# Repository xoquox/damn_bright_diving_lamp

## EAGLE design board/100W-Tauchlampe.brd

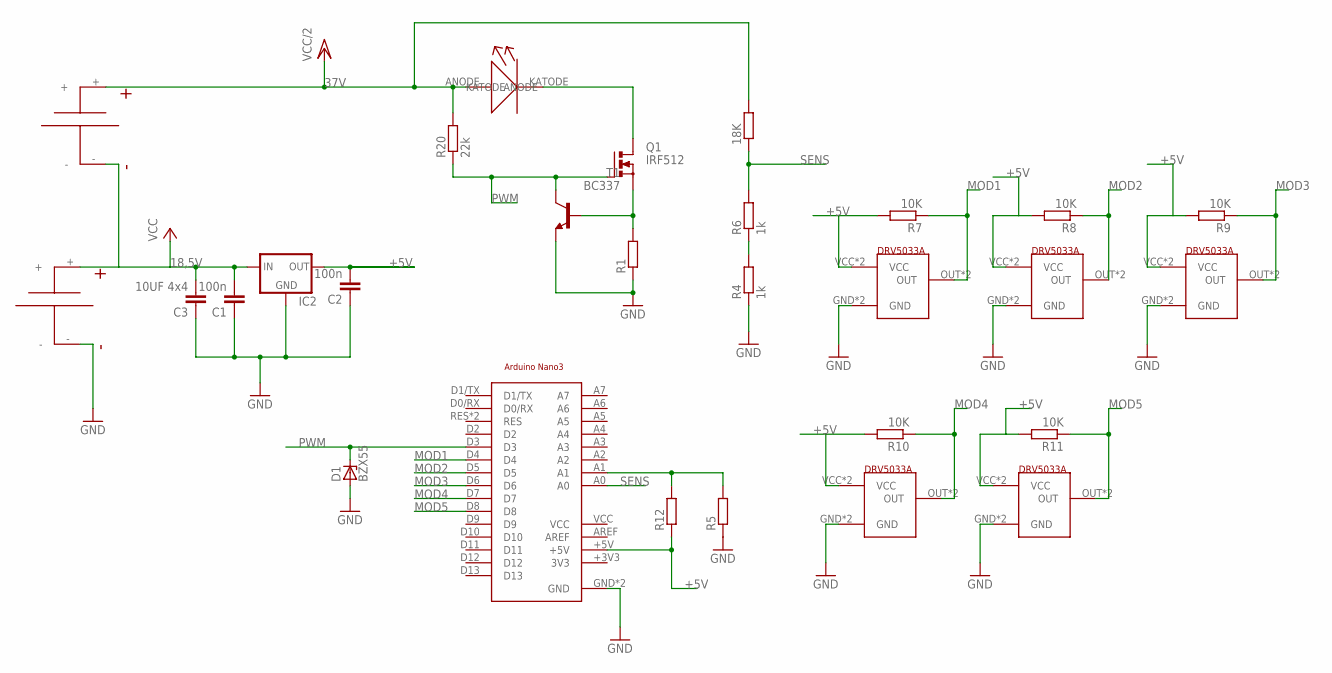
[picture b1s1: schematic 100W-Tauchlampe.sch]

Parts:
1, 2, 3, 4, 5: DRV5033AJQLPGM; T92/SOT23
18K: R-EU_R0805; R0805
C1, C2: 100n; C0603
C3: 10UF 4x4; 4X4
D1: BZX55; DO35Z10
IC2: 78XXS
Q1: IRF512; TO220BV
R1: R-EU_0207/2V; 0207/2V
R4, R6: 1k; R0805
R5: R-EU_R0805; R0805
R7, R8, R9, R10, R11: 10K; R0805
R12: R-EU_0204/2V; 0204V
R20: 22k; 0204V
T1: BC337; TO92
U$1: ARDUINO-NANO3
U$7: 100W-LED
U$8, U$9: AKKU; AKKUSMD

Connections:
18,5V: C1.2, C3.P$2 (2), IC2.IN, U$8.-, U$9.+
37V: 18K.2, R20.2, U$7.ANODE, U$8.+
+5V: 2.VCC, 2.VCC/SMD (VCC), 3.VCC, 3.VCC/SMD (VCC), 5.VCC, 5.VCC/SMD (VCC), C2.2, IC2.OUT, R8.2, R9.2, R11.2, R12.1, U$1.+5V
GND: 1.GND, 1.GND/SMD (GND), 2.GND, 2.GND/SMD (GND), 3.GND, 3.GND/SMD (GND), 4.GND, 4.GND/SMD (GND), 5.GND, 5.GND/SMD (GND), C1.1, C2.1, C3.1, D1.A, IC2.GND, R1.1, R4.1, R5.1, T1.1 (E), U$1.GND, U$1.GND2 (GND), U$9.-
MOD1: 1.OUT, 1.OUT/SMD (OUT), R7.1, U$1.D4
MOD2: 2.OUT, 2.OUT/SMD (OUT), R8.1, U$1.D5
MOD3: 3.OUT, 3.OUT/SMD (OUT), R9.1, U$1.D6
MOD4: 4.OUT, 4.OUT/SMD (OUT), R10.1, U$1.D7
MOD5: 5.OUT, 5.OUT/SMD (OUT), R11.1, U$1.D8
unnamed: R5.2, R12.2, U$1.A1
unnamed: Q1.S, R1.2, T1.2 (B)
unnamed: 1.VCC, 1.VCC/SMD (VCC), R7.2
unnamed: Q1.D, U$7.KATODE
unnamed: 4.VCC, 4.VCC/SMD (VCC), R10.2
unnamed: R4.2, R6.1
PWM: D1.C, Q1.G, R20.1, T1.3 (C), U$1.D3
SENS: 18K.1, R6.2, U$1.A0

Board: 2 copper layers, 28 parts (0 on the bottom side), 17 nets, no tracks yet.

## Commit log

2014-04-19 init commit
2014-04-19 add stl files
2014-04-19 move to directory
2014-04-19 added frontdesign dir and files
2014-04-19 remove wrong file
2014-11-15 added first version of source
2014-11-16 added first board version
2014-11-16 reviewed first version, some minor errors fixed
2018-09-04 Akkuplatine hinzugefügt
